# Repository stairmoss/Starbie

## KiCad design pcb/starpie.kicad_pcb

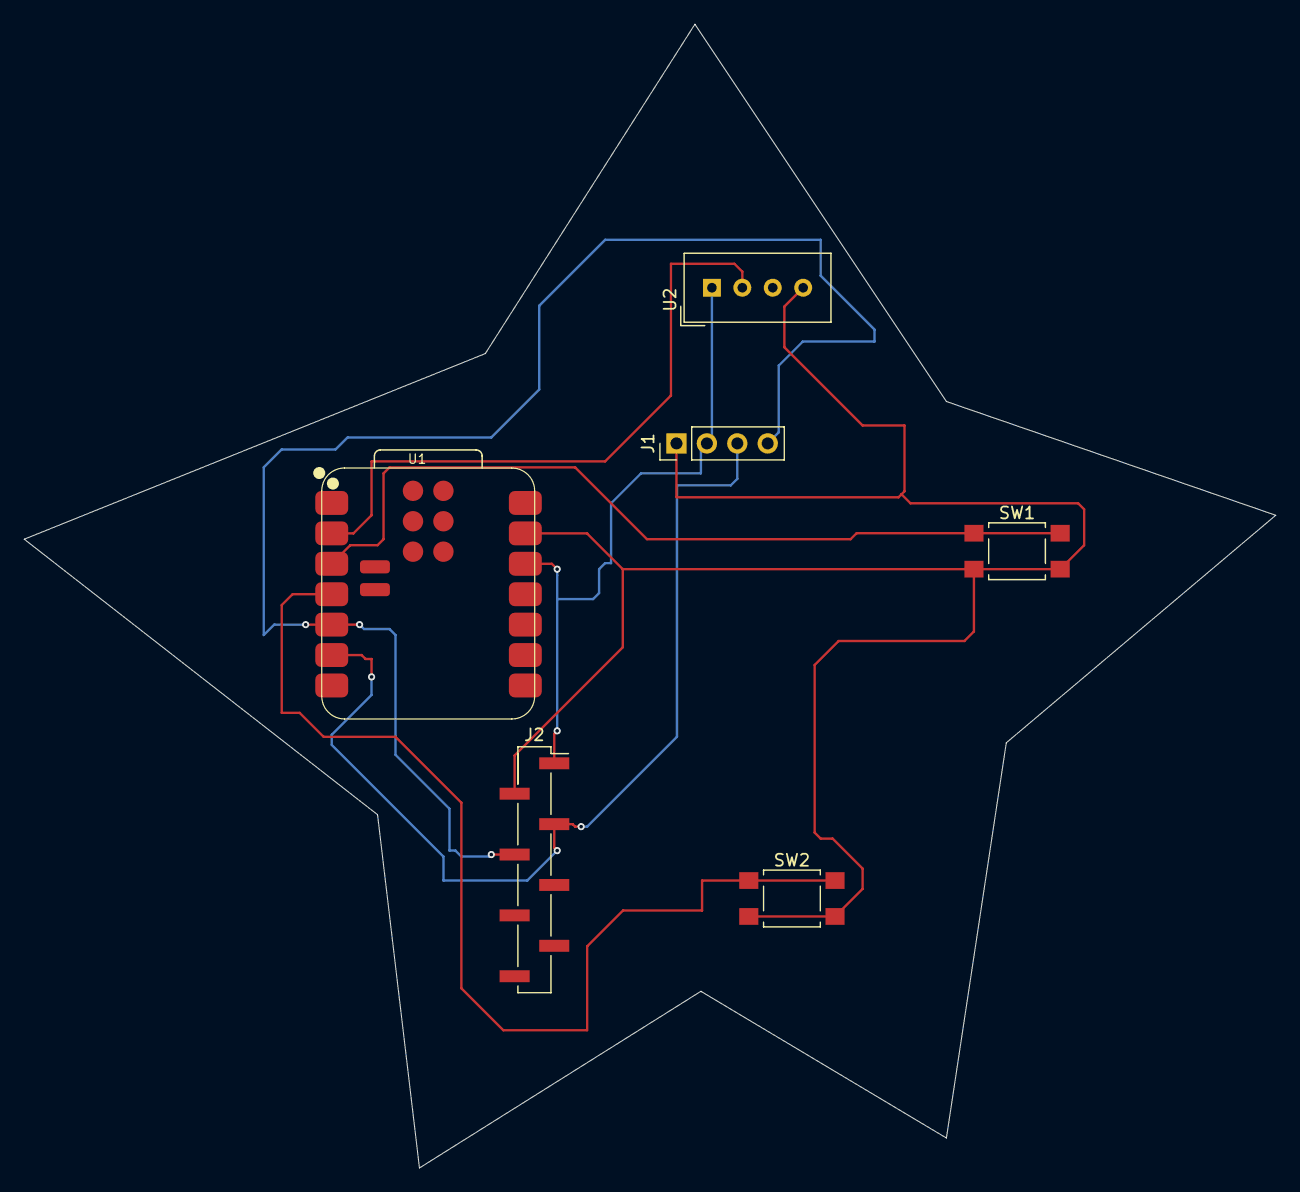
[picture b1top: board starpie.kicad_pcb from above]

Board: 2 copper layers, 104.5 x 95.5 mm, 6 parts (0 on the bottom side), 7 nets.

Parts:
J1: Conn_01x04_Pin; PinHeader_1x04_P2.54mm_Vertical
J2: Conn_01x08_Pin; PinHeader_1x08_P2.54mm_Vertical_SMD_Pin1Right
SW1, SW2: SW_Push; SW_SPST_TL3305B
U1: XIAO-ESP32-C3-SMD
U2: DHT11; Aosong_DHT11_5.5x12.0_P2.54mm

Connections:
+3.3V: J1.2, J2.1, U1.12 (3V3_OUT), U2.1 (VDD)
/BTN1: SW1.1, U1.3 (D2)
/BTN2: SW2.1, U1.4 (D3)
/DHT_DATA: U1.2 (D1), U2.2 (DATA)
/SCL: J1.3, J2.3, U1.6 (D5)
/SDA: J1.4, J2.4, U1.5 (D4)
GND: J1.1, J2.2, SW1.2, SW2.2, U1.13 (GND), U2.4 (GND)
